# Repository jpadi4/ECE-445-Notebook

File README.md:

# ECE 445 Group 78
Digital lab notebook based off of this project: https://github.com/OfficialPouya/Safety_Suite_For_Electric_Longboard

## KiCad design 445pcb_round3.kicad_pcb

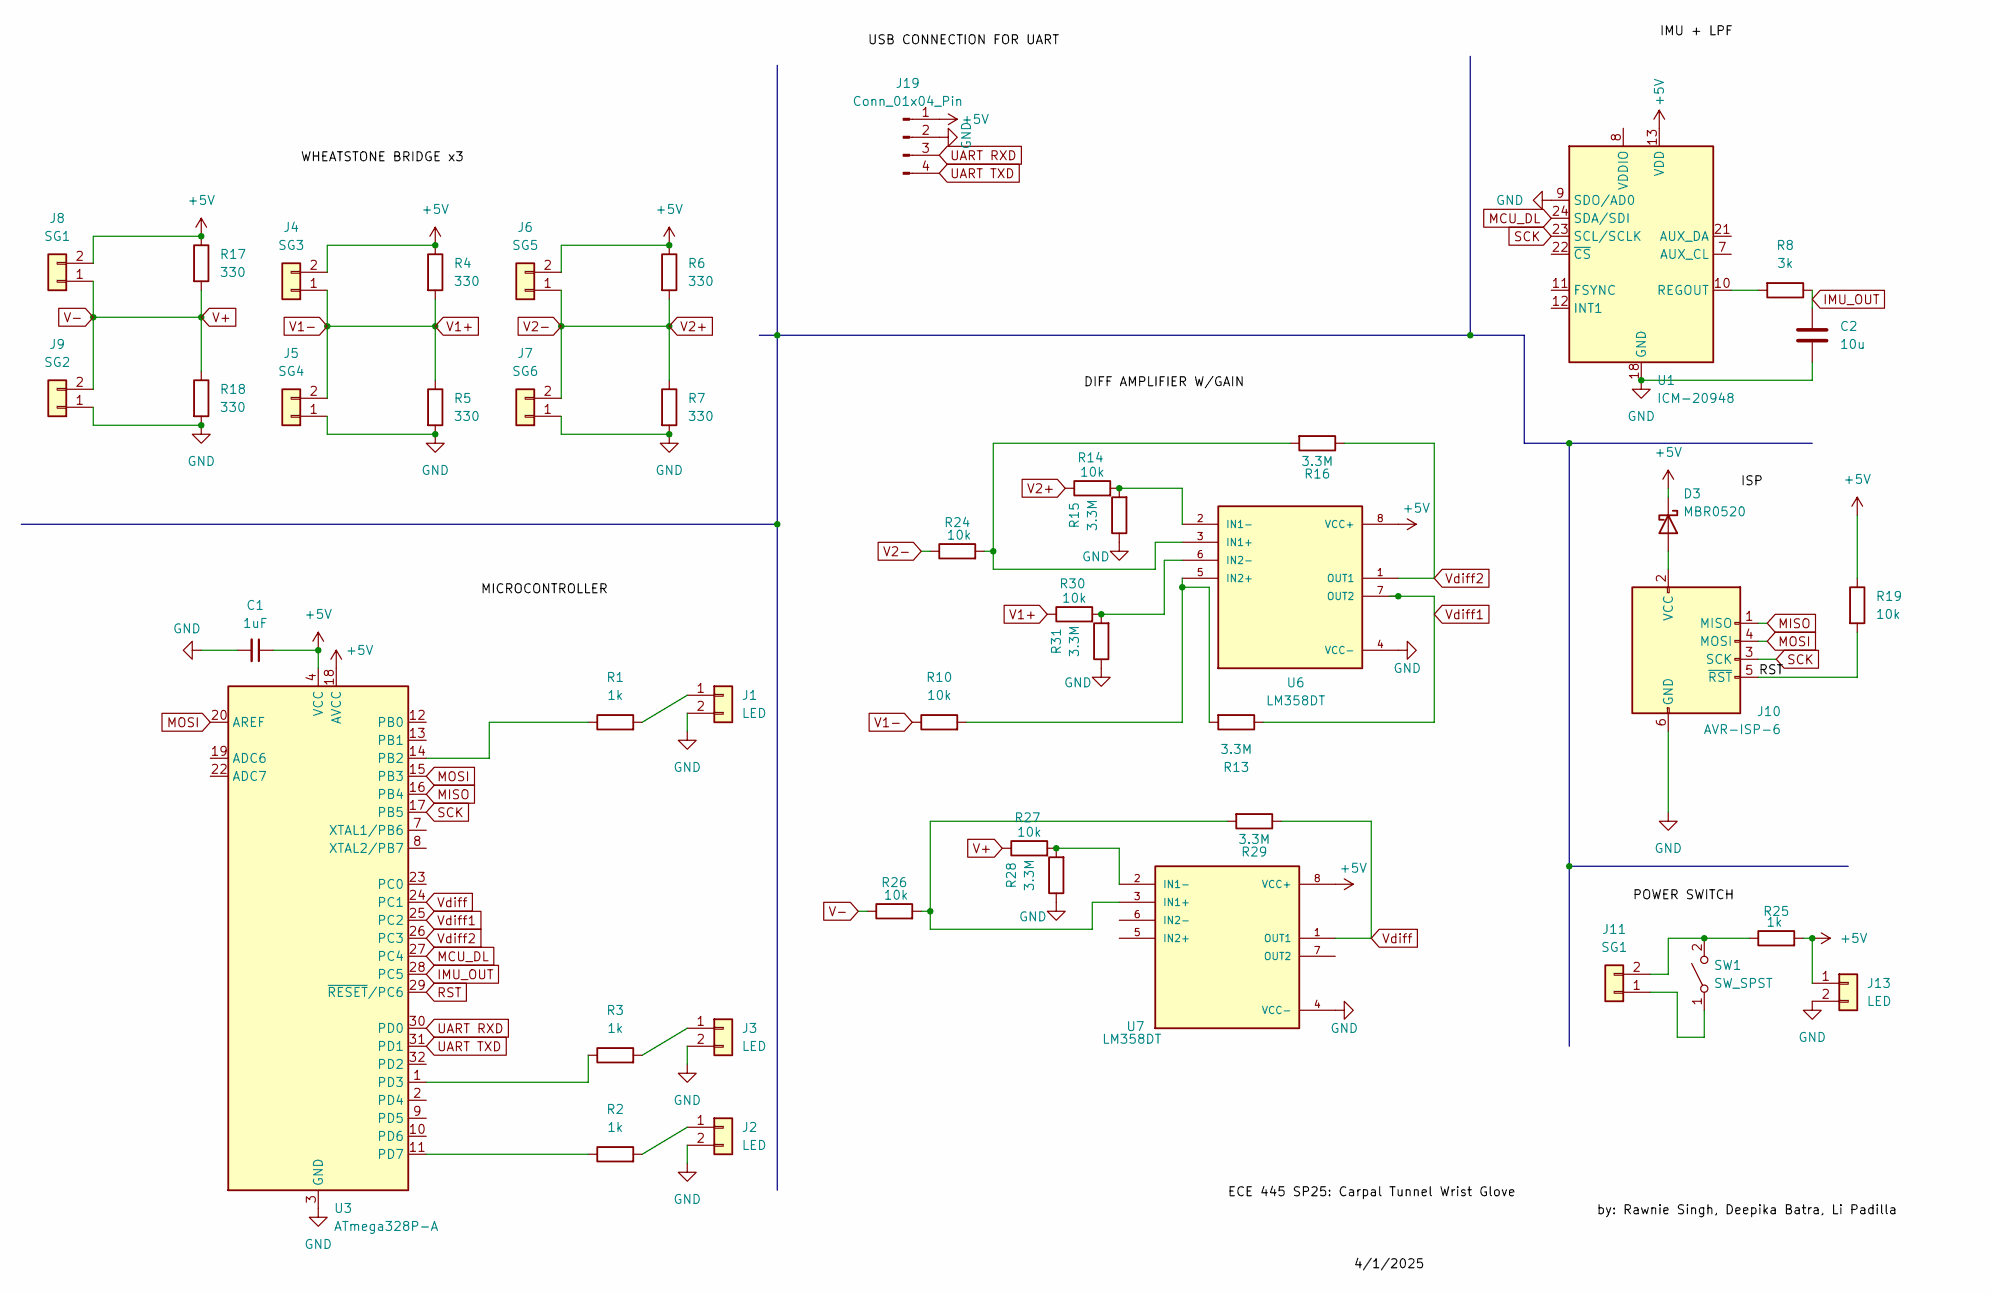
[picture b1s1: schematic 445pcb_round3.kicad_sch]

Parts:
C1: 1uF; C_0805_2012Metric_Pad1.18x1.45mm_HandSolder
C2: 10u; C_0805_2012Metric_Pad1.18x1.45mm_HandSolder
D3: MBR0520; D_SOD-123
J1, J2, J3, J13: LED; Molex_KK-254_AE-6410-02A_1x02_P2.54mm_Vertical
J4: SG3; Molex_KK-254_AE-6410-02A_1x02_P2.54mm_Vertical
J5: SG4; Molex_KK-254_AE-6410-02A_1x02_P2.54mm_Vertical
J6: SG5; Molex_KK-254_AE-6410-02A_1x02_P2.54mm_Vertical
J7: SG6; Molex_KK-254_AE-6410-02A_1x02_P2.54mm_Vertical
J8, J11: SG1; Molex_KK-254_AE-6410-02A_1x02_P2.54mm_Vertical
J9: SG2; Molex_KK-254_AE-6410-02A_1x02_P2.54mm_Vertical
J10: AVR-ISP-6; IDC-Header_2x03_P2.54mm_Vertical
J19: Conn_01x04_Pin; Molex_KK-254_AE-6410-04A_1x04_P2.54mm_Vertical
R1, R2, R3, R25: 1k; R_0805_2012Metric_Pad1.20x1.40mm_HandSolder
R4, R5, R6, R7, R17, R18: 330; R_0805_2012Metric_Pad1.20x1.40mm_HandSolder
R8: 3k; R_0805_2012Metric_Pad1.20x1.40mm_HandSolder
R10, R14, R19, R24, R26, R27, R30: 10k; R_0805_2012Metric_Pad1.20x1.40mm_HandSolder
R13, R15, R16, R28, R29, R31: 3.3M; R_0805_2012Metric_Pad1.20x1.40mm_HandSolder
SW1: SW_SPST; SW_DIP_SPSTx01_Slide_9.78x4.72mm_W7.62mm_P2.54mm
U1: ICM-20948; InvenSense_QFN-24_3x3mm_P0.4mm
U3: ATmega328P-A; TQFP-32_7x7mm_P0.8mm
U6, U7: LM358DT; SOIC-8_3.9x4.9mm_P1.27mm

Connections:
+5V: C1.1, D3.1 (K), J4.2, J6.2, J8.2, J13.1, J19.1, R4.1, R6.1, R17.1, R19.1, R25.2, U1.13 (VDD), U3.4 (VCC), U3.6 (VCC), U3.18 (AVCC), U6.8 (VCC+), U7.8 (VCC+)
GND: C1.2, C2.2, J1.2, J2.2, J3.2, J5.1, J7.1, J9.1, J10.6 (GND), J13.2, J19.2, R5.2, R7.2, R15.1, R18.2, R28.1, R31.1, U1.9 (SDO/AD0), U1.18 (GND), U1.20 (GND), U3.3 (GND), U3.5 (GND), U3.21 (GND), U6.4 (VCC-), U7.4 (VCC-)
IMU_OUT: C2.1, R8.1, U3.28 (PC5)
MCU_DL: U1.24 (SDA/SDI), U3.27 (PC4)
MISO: J10.1 (MISO), U3.16 (PB4)
MOSI: J10.4 (MOSI), U3.15 (PB3), U3.20 (AREF)
unnamed: D3.2 (A), J10.2 (VCC)
unnamed: J1.1, R1.2
unnamed: J2.1, R2.2
unnamed: J3.1, R3.2
unnamed: J11.1, SW1.1 (A)
unnamed: J11.2, R25.1, SW1.2 (B)
unnamed: R8.2, U1.10 (REGOUT)
unnamed: R1.1, U3.14 (PB2)
unnamed: R3.1, U3.1 (PD3)
unnamed: R2.1, U3.11 (PD7)
unnamed: R16.2, R24.2, U6.3 (IN1+)
unnamed: R14.2, R15.2, U6.2 (IN1-)
unnamed: R10.2, R13.2, U6.5 (IN2+)
unnamed: R30.2, R31.2, U6.6 (IN2-)
unnamed: R26.2, R29.2, U7.3 (IN1+)
unnamed: R27.2, R28.2, U7.2 (IN1-)
RST: J10.5 (~RST), R19.2, U3.29 (~RESET/PC6)
SCK: J10.3 (SCK), U1.23 (SCL/SCLK), U3.17 (PB5)
UART RXD: J19.3, U3.30 (PD0)
UART TXD: J19.4, U3.31 (PD1)
V1+: J4.1, J5.2, R4.2, R5.1, R10.1, R30.1
V2+: J6.1, J7.2, R6.2, R7.1, R14.1, R24.1
V+: J8.1, J9.2, R17.2, R18.1, R26.1, R27.1
Vdiff: R29.1, U3.24 (PC1), U7.1 (OUT1)
Vdiff1: R13.1, U3.25 (PC2), U6.7 (OUT2)
Vdiff2: R16.1, U3.26 (PC3), U6.1 (OUT1)

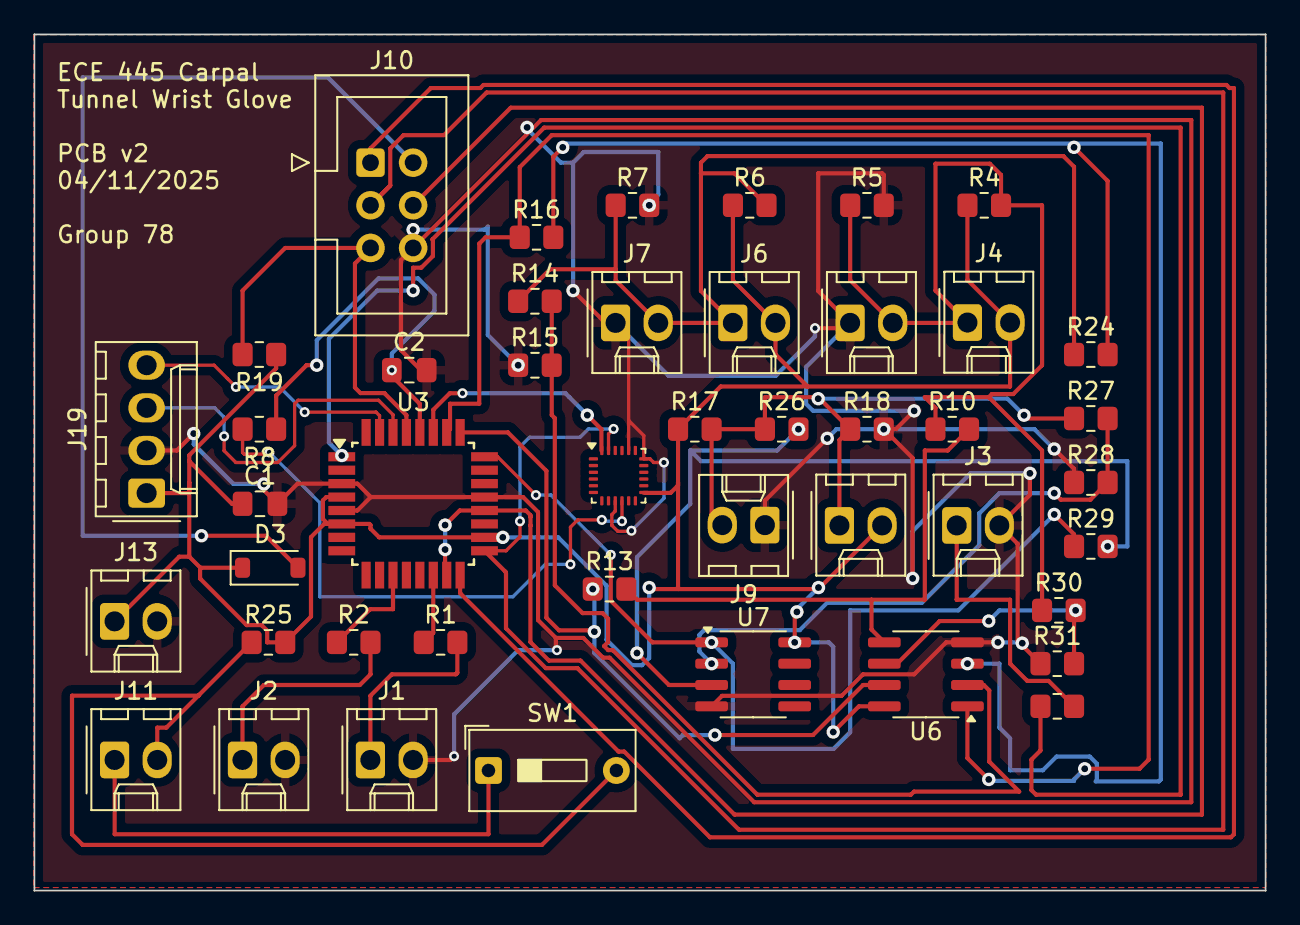
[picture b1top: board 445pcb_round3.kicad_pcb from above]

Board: 2 copper layers, 73.3 x 51.0 mm, 45 parts (0 on the bottom side), 32 nets.

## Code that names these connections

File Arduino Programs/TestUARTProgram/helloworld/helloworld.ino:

#define LED1 PIN_PB2    // Pin for LED1 output
#define LED2 PIN_PD3    // Pin for LED2 output
#define LED3 PIN_PD7    // Pin for LED3 output

#define vdiff PIN_PC1     // Pin for wheatstone bridge 1 signal input
#define vdiff1 PIN_PC2    // Pin for wheatstone bridge 2 signal input
#define vdiff2 PIN_PC3    // Pin for wheatstone bridge 3 signal input

#define imu PIN_PC5       // Pin for IMU signal input

void setup() {
  // sensor layer subsystem inputs
  pinMode(vdiff, INPUT);
  pinMode(vdiff1, INPUT);
  pinMode(vdiff2, INPUT);
  pinMode(imu, INPUT);

  // communication subsystem LEDs
  pinMode(LED1, OUTPUT);
  pinMode(LED2, OUTPUT);
  pinMode(LED3, OUTPUT);

  Serial.begin(9600);  // Initialize serial communication at 9600 baud
}

void loop() {
  Serial.println("Hello World!");  // MCU sends "Hello World" followed by a newline

  // turn on all LEDs
  digitalWrite(LED1, HIGH);
  digitalWrite(LED2, HIGH);
  digitalWrite(LED3, HIGH);
  
  delay(1000);  // Wait 1 second before repeating
}

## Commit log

2025-01-28 Add subdirectories for Rawnie and Li
2025-01-28 Add reference for digital lab notebook setup
2025-02-11 Add directory for Deepika
2025-02-11 Rename directories
2025-02-11 Initialize notebooks
2025-02-11 Team contract document
2025-02-11 Add meeting minutes directory and document for meetings with TAs
2025-02-12 Uploading meeting minutes for first meeting with TA
2025-02-18 new directory, feb 18 meeting minutes
2025-03-07 Pushed meetings
2025-03-07 Update Li Padilla notebook
2025-03-07 Mistakenly put 2024 instead of 2025
2025-03-07 Complete meeting notes for 3/7/25
2025-03-09 Push 3/9 meeting (part 1)
2025-03-09 update notebook
2025-03-09 3/9/25 part 1 meeting
2025-03-10 Add new Arduino program
2025-03-10 Push Breadboard Demo .ino code file
2025-03-10 update meetings with image
2025-03-10 Push demo code
2025-04-02 kicad round3 schematic
2025-04-02 pcb_schematic_version2
2025-04-06 Pushing local entries to git repo
2025-04-15 notebook meetings update
2025-04-16 Explained LED program for 3 strain gauges
2025-04-20 test programs for LED on PCB
2025-04-20 Update the test LED program for 3 wheatstone bridges to use the proper pins
2025-04-20 Upload backup PCB files, update team meeting agendas
2025-04-20 Update LED programs; create Program to just light up LEDs
2025-04-23 more meeting notes
2025-04-24 update journal entries
2025-04-24 adding power to op-amps, switching USB to connector, zener diode
2025-04-24 IMU connections for new PCB
2025-04-28 add some images, update entries
2025-04-29 add 4/28 meeting
2025-04-29 successful hello world UART program + run
2025-04-29 working analog to digital conversion program
2025-04-30 add some research done for the IMU
2025-04-30 notes on grounding capacitor for schottky schematic
2025-04-30 add IMU code to test reading REGOUT
2025-04-30 add arduino program to read all of the sensor signals and output to UART
2025-04-30 analogrd.ino does not do voltage conversion
2025-04-30 testserialoutput only outputs analog value
2025-04-30 Clean up repository folders
2025-04-30 change serial output to simplify string processing
2025-04-30 python code
2025-04-30 updated line format
2025-04-30 added stretch imgs, pop-up message code, new function for reading vdiff for 2 bridges
2025-04-30 update anolog read for better string parsing
2025-05-08 updating lab notebook.md
2025-05-08 2112025.md
2025-05-09 mock IMU data + analysis
2025-05-09 update 250423.md with correct schematic
2025-05-09 updating entries.md
2025-05-09 adding diagrams.md
2025-05-09 adding testing details.md
